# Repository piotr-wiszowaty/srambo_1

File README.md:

srambo\_1
========

srambo\_1 is a yet another 320 kB [Atari](https://en.wikipedia.org/wiki/Atari_8-bit_family) XE memory expansion. It designed for
Atari 130 XEs and 65 XEs with ECI connector.

Description
-----------

The device has two modes of operation (selected with a jumper):

1. 'Rambo' - extended memory banks are selected with PORTB bits 2, 3, 5, 6.
   Access to extended memory by both CPU and ANTIC is controlled with PORTB
   bit 4.
   To turn on this mode one needs to connect pins AUX3 and AUX4 together.
2. 'Compy' - extended memory banks are selected with PORTB bits 2, 3, 6, 7.
   Access to extended memory by CPU is controlled with PORTB bit 4. Access to
   extended memory by ANTIC is controlled with PORTB bit 5.
   To select this mode one needs to connect pins AUX3 and AUX2 together.

Sources
-------

`cpld/` - CPLD design files (ISE WebPack 14.7)

`pcb/`  - PCB design files (Kicad 4.0.3)

Installation
------------

All Atari modifications are easily reversible (provided one does not - for
example - destroy any tracks during desoldering process).
To install the expansion one needs to:

0. Assemble the memory expansion (obviously)
1. Desolder all DRAM chips (U9..U16, U26..U33)
2. Desolder MMU chip (U34)
3. Desolder EMMU chip U3 (130 XE) or three wire jumpers (65 XE)
4. Solder a wire between U23 PIA pin 16 and U3 EMMU pin 12
5. Solder appropriate pin-header sockets into the motherboard (see PCB design
   files for reference)
6. Plug the assembled device into the sockets

References
----------

Various parts of control logic are based on [576 kB memory expansion](http://atarionline.pl/v01/index.php?subaction=showfull&id=1235583828&archive=&start_from=0&ucat=6&ct=wynalazki&amp%253Bamp%253Bucat=1%253Bamp%253Bsubaction%253Dshowfull%252Ftrackback) by ASAL.

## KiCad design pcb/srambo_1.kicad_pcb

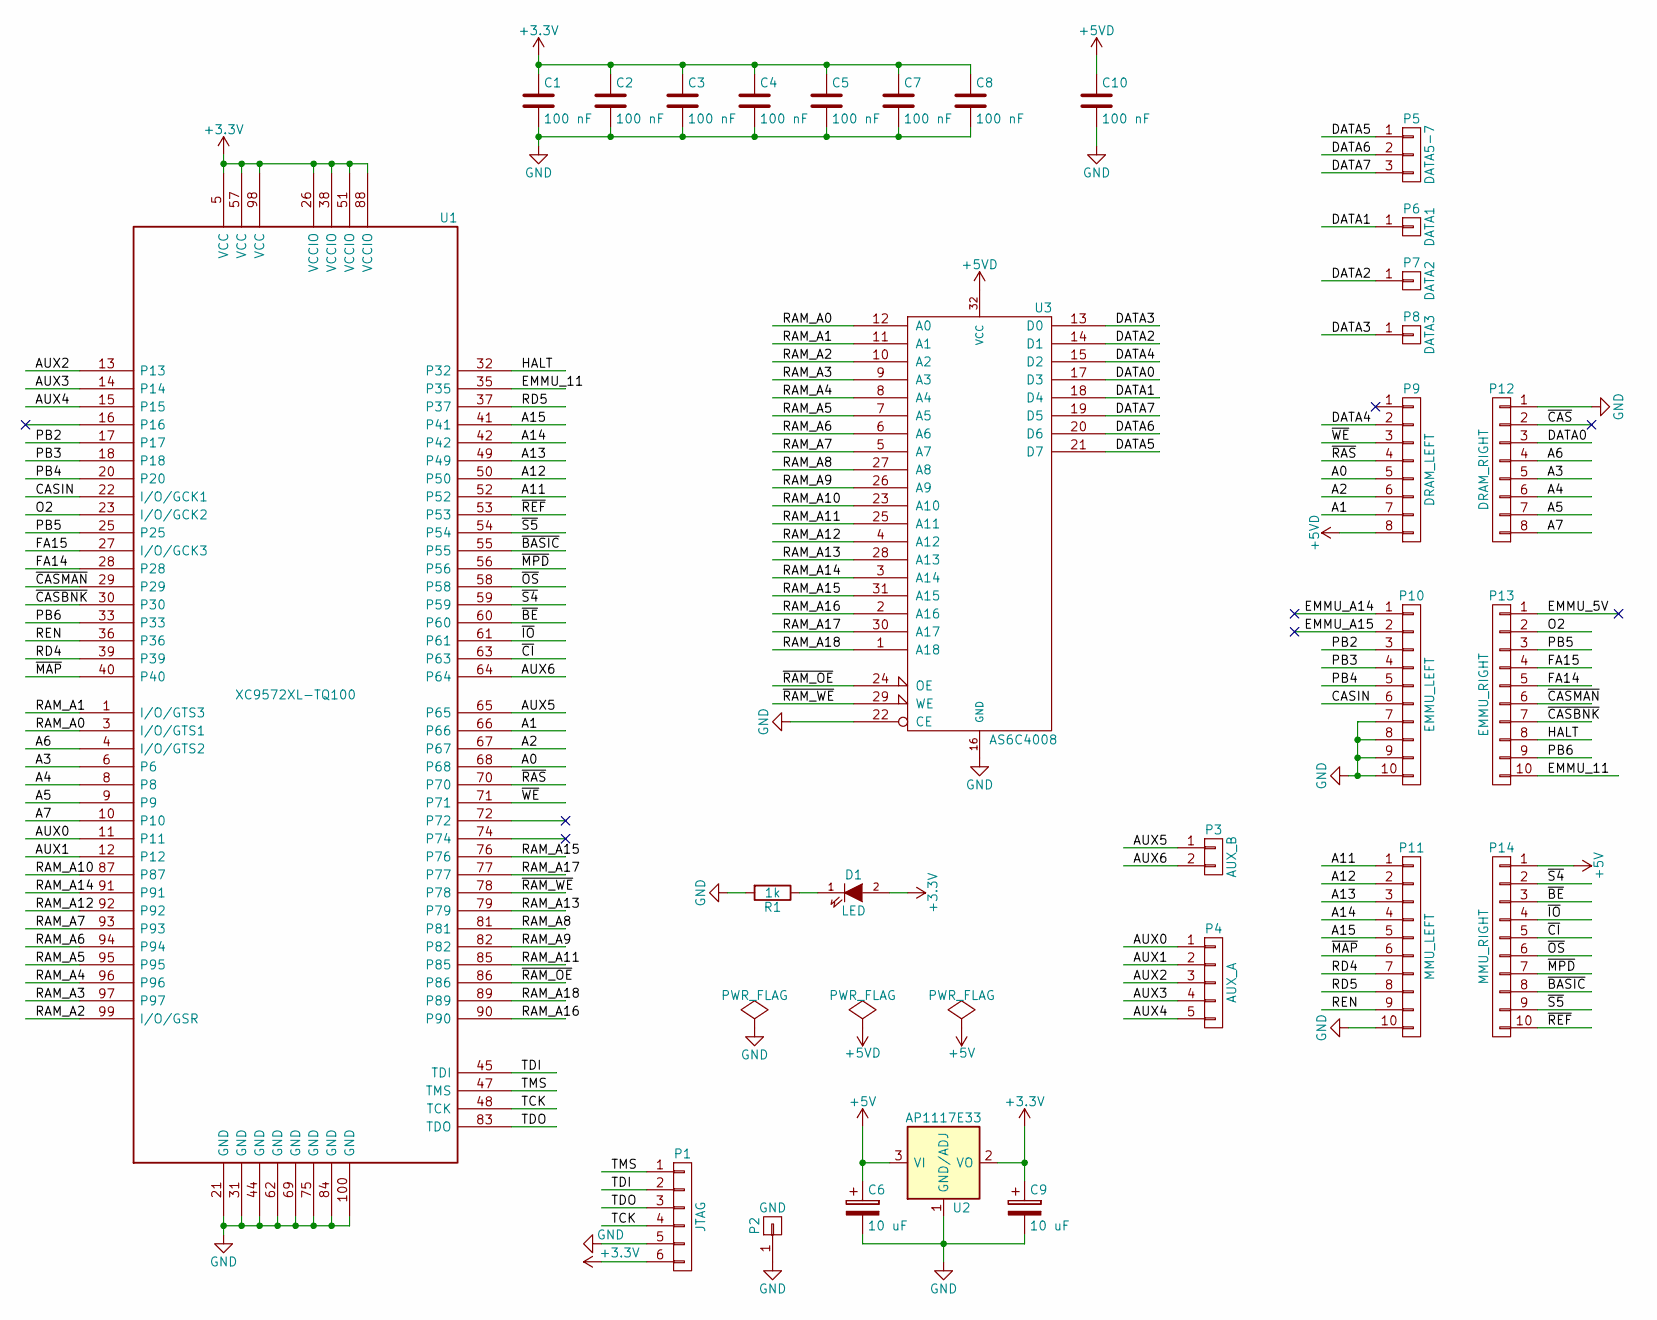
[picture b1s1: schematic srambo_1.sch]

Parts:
C1, C2, C3, C4, C5, C7, C8, C10: 100 nF; C_0805_HandSoldering
C6, C9: 10 uF; TantalC_SizeB_EIA-3528_HandSoldering
D1: LED; LED_0805
P1: JTAG; Pin_Header_Straight_1x06
P2: GND; Pin_Header_Straight_1x01
P3: AUX_B; Pin_Header_Straight_1x02
P4: AUX_A; Pin_Header_Straight_1x05
P5: DATA5-7; Pin_Header_Straight_1x03
P6: DATA1; Pin_Header_Straight_1x01
P7: DATA2; Pin_Header_Straight_1x01
P8: DATA3; Pin_Header_Straight_1x01
P9: DRAM_LEFT; Pin_Header_Straight_1x08
P10: EMMU_LEFT; Pin_Header_Straight_1x10
P11: MMU_LEFT; Pin_Header_Straight_1x10
P12: DRAM_RIGHT; Pin_Header_Straight_1x08
P13: EMMU_RIGHT; Pin_Header_Straight_1x10
P14: MMU_RIGHT; Pin_Header_Straight_1x10
R1: 1k; R_0805_HandSoldering
U1: XC9572XL-TQ100; TQFP-100_14x14mm_Pitch0.5mm
U2: AP1117E33; TO-252-2Lead
U3: AS6C4008; TSOP-II-32_21.0x10.2mm_Pitch1.27mm

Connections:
+3V3: C1.1, C2.1, C3.1, C4.1, C5.1, C7.1, C8.1, C9.1, D1.2 (A), P1.6, U1.5 (VCC), U1.26 (VCCIO), U1.38 (VCCIO), U1.51 (VCCIO), U1.57 (VCC), U1.88 (VCCIO), U1.98 (VCC), U2.2 (VO)
+5V: C6.1, P14.1, U2.3 (VI)
+5VD: C10.1, P9.8, U3.32 (VCC)
/A0: P9.5, U1.68
/A1: P9.7, U1.66
/A2: P9.6, U1.67
/A3: P12.5, U1.6
/A4: P12.6, U1.8
/A5: P12.7, U1.9
/A6: P12.4, U1.4 (I/O/GTS2)
/A7: P12.8, U1.10
/A11: P11.1, U1.52
/A12: P11.2, U1.50
/A13: P11.3, U1.49
/A14: P11.4, U1.42
/A15: P11.5, U1.41
/AUX0: P4.1, U1.11
/AUX1: P4.2, U1.12
/AUX2: P4.3, U1.13
/AUX3: P4.4, U1.14
/AUX4: P4.5, U1.15
/AUX5: P3.1, U1.65
/AUX6: P3.2, U1.64
/CASIN: P10.6, U1.22 (I/O/GCK1)
/DATA0: P12.3, U3.17 (D3)
/DATA1: P6.1, U3.18 (D4)
/DATA2: P7.1, U3.14 (D1)
/DATA3: P8.1, U3.13 (D0)
/DATA4: P9.2, U3.15 (D2)
/DATA5: P5.1, U3.21 (D7)
/DATA6: P5.2, U3.20 (D6)
/DATA7: P5.3, U3.19 (D5)
/EMMU_5V: P13.1
/EMMU_11: P13.10, U1.35
/EMMU_A14: P10.1
/EMMU_A15: P10.2
/FA14: P13.5, U1.28
/FA15: P13.4, U1.27 (I/O/GCK3)
/HALT: P13.8, U1.32
/O2: P13.2, U1.23 (I/O/GCK2)
/PB2: P10.3, U1.17
/PB3: P10.4, U1.18
/PB4: P10.5, U1.20
/PB5: P13.3, U1.25
/PB6: P13.9, U1.33
/RAM_A0: U1.3 (I/O/GTS1), U3.12 (A0)
/RAM_A1: U1.1 (I/O/GTS3), U3.11 (A1)
/RAM_A2: U1.99 (I/O/GSR), U3.10 (A2)
/RAM_A3: U1.97, U3.9 (A3)
/RAM_A4: U1.96, U3.8 (A4)
/RAM_A5: U1.95, U3.7 (A5)
/RAM_A6: U1.94, U3.6 (A6)
/RAM_A7: U1.93, U3.5 (A7)
/RAM_A8: U1.81, U3.27 (A8)
/RAM_A9: U1.82, U3.26 (A9)
/RAM_A10: U1.87, U3.23 (A10)
/RAM_A11: U1.85, U3.25 (A11)
/RAM_A12: U1.92, U3.4 (A12)
/RAM_A13: U1.79, U3.28 (A13)
/RAM_A14: U1.91, U3.3 (A14)
/RAM_A15: U1.76, U3.31 (A15)
/RAM_A16: U1.90, U3.2 (A16)
/RAM_A17: U1.77, U3.30 (A17)
/RAM_A18: U1.89, U3.1 (A18)
/RD4: P11.7, U1.39
/RD5: P11.8, U1.37
/REN: P11.9, U1.36
/TCK: P1.4, U1.48 (TCK)
/TDI: P1.2, U1.45 (TDI)
/TDO: P1.3, U1.83 (TDO)
/TMS: P1.1, U1.47 (TMS)
/~BASIC: P14.8, U1.55
/~BE: P14.3, U1.60
/~CAS: P12.2
/~CASBNK: P13.7, U1.30
/~CASMAN: P13.6, U1.29
/~CI: P14.5, U1.63
/~IO: P14.4, U1.61
/~MAP: P11.6, U1.40
/~MPD: P14.7, U1.56
/~OS: P14.6, U1.58
/~RAM_OE: U1.86, U3.24 (OE)
/~RAM_WE: U1.78, U3.29 (WE)
/~RAS: P9.4, U1.70
/~REF: P14.10, U1.53
/~S4: P14.2, U1.59
/~S5: P14.9, U1.54
/~WE: P9.3, U1.71
GND: C1.2, C2.2, C3.2, C4.2, C5.2, C6.2, C7.2, C8.2, C9.2, C10.2, P1.5, P2.1, P10.7, P10.8, P10.9, P10.10, P11.10, P12.1, R1.2, U1.21 (GND), U1.31 (GND), U1.44 (GND), U1.62 (GND), U1.69 (GND), U1.75 (GND), U1.84 (GND), U1.100 (GND), U2.1 (GND/ADJ), U3.16 (GND), U3.22 (CE)
unnamed: D1.1 (K), R1.1

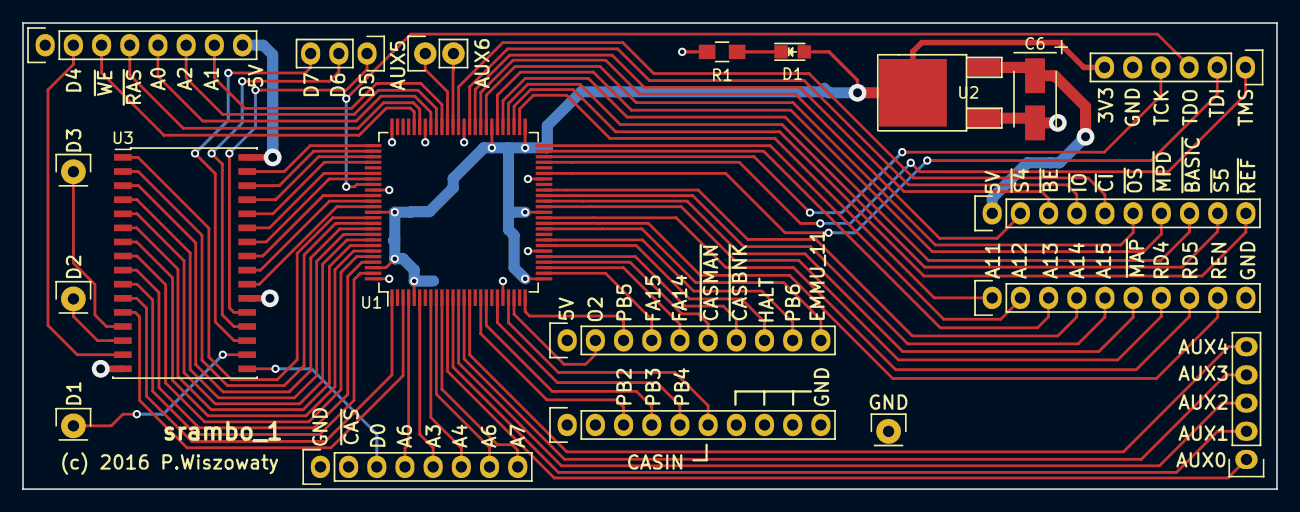
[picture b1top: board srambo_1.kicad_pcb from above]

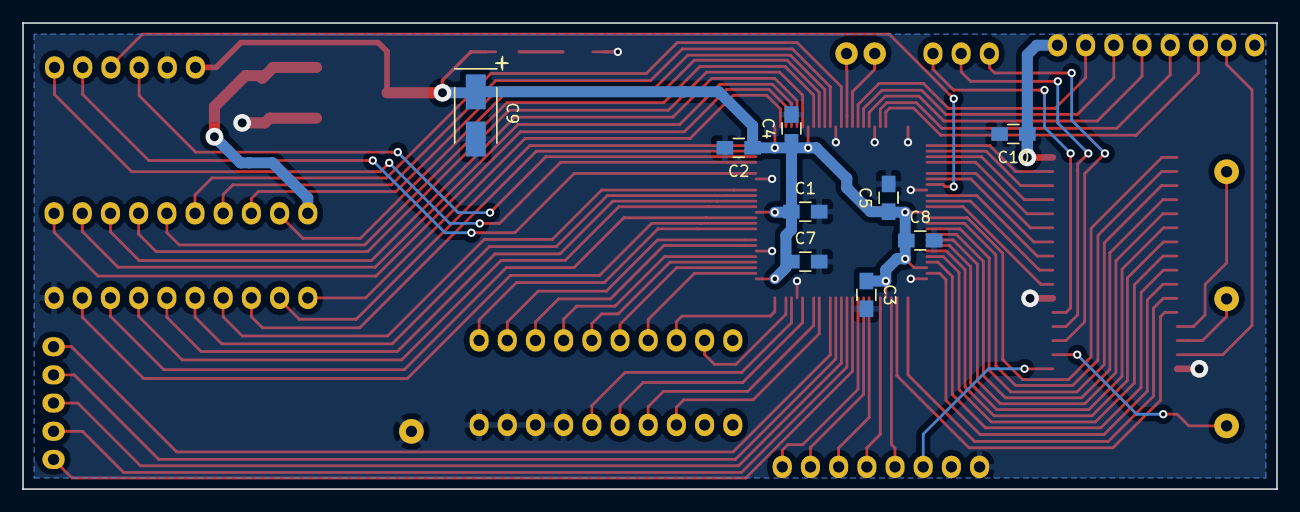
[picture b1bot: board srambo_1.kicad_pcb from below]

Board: 2 copper layers, 113.0 x 42.0 mm, 29 parts (9 on the bottom side), 86 nets.

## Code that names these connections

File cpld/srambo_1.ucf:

net "aux0" loc = p11;
net "aux1" loc = p12;
net "aux2" loc = p13;
net "aux3" loc = p14;
net "aux4" loc = p15;
net "aux5" loc = p65;
net "aux6" loc = p64;

net "pb2" loc = p17;
net "pb3" loc = p18;
net "pb4" loc = p20;
net "pb5" loc = p25;
net "pb6" loc = p33;

net "casin" loc = p22;
net "o2" loc = p23;
net "fa14" loc = p28;
net "fa15" loc = p27;
net "n_map" loc = p40;
net "rd4" loc = p39;
net "rd5" loc = p37;
net "ren" loc = p36;
net "n_os" loc = p58;
net "n_ci" loc = p63;
net "n_io" loc = p61;
net "n_be" loc = p60;
net "n_s4" loc = p59;
net "n_s5" loc = p54;
net "n_mpd" loc = p56;
net "n_basic" loc = p55;
net "n_ref" loc = p53;
net "n_ras" loc = p70;
net "n_we" loc = p71;

net "casman" loc = p29;
net "casbnk" loc = p30;
net "emmu_11" loc = p35;
net "halt" loc = p32;

net "a0" loc = p68;
net "a1" loc = p66;
net "a2" loc = p67;
net "a3" loc = p6;
net "a4" loc = p8;
net "a5" loc = p9;
net "a6" loc = p4;
net "a7" loc = p10;
net "a11" loc = p52;
net "a12" loc = p50;
net "a13" loc = p49;
net "a14" loc = p42;
net "a15" loc = p41;

net "ram_addr<0>" loc = p3;
net "ram_addr<1>" loc = p1;
net "ram_addr<2>" loc = p99;
net "ram_addr<3>" loc = p97;
net "ram_addr<4>" loc = p96;
net "ram_addr<5>" loc = p95;
net "ram_addr<6>" loc = p94;
net "ram_addr<7>" loc = p93;
net "ram_addr<8>" loc = p81;
net "ram_addr<9>" loc = p82;
net "ram_addr<10>" loc = p87;
net "ram_addr<11>" loc = p85;
net "ram_addr<12>" loc = p92;
net "ram_addr<13>" loc = p79;
net "ram_addr<14>" loc = p91;
net "ram_addr<15>" loc = p76;
net "ram_addr<16>" loc = p90;
net "ram_addr<17>" loc = p77;
net "ram_addr<18>" loc = p89;
net "ram_n_we" loc = p78;
net "ram_n_oe" loc = p86;

NET "o2" BUFG = CLK;
NET "o2" TNM_NET = "grp_o2";
TIMESPEC "TS_o2" = PERIOD "grp_o2" 561 ns HIGH 40%;
NET "pb5" BUFG = DATA_GATE;

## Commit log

2016-09-10 Add sources
2016-11-21 PCB: Update symbols
2016-11-21 PCB: Add OSHW logo

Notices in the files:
pcb/srambo_1.kicad_pcb:
(c) 2016 P.Wiszowaty
